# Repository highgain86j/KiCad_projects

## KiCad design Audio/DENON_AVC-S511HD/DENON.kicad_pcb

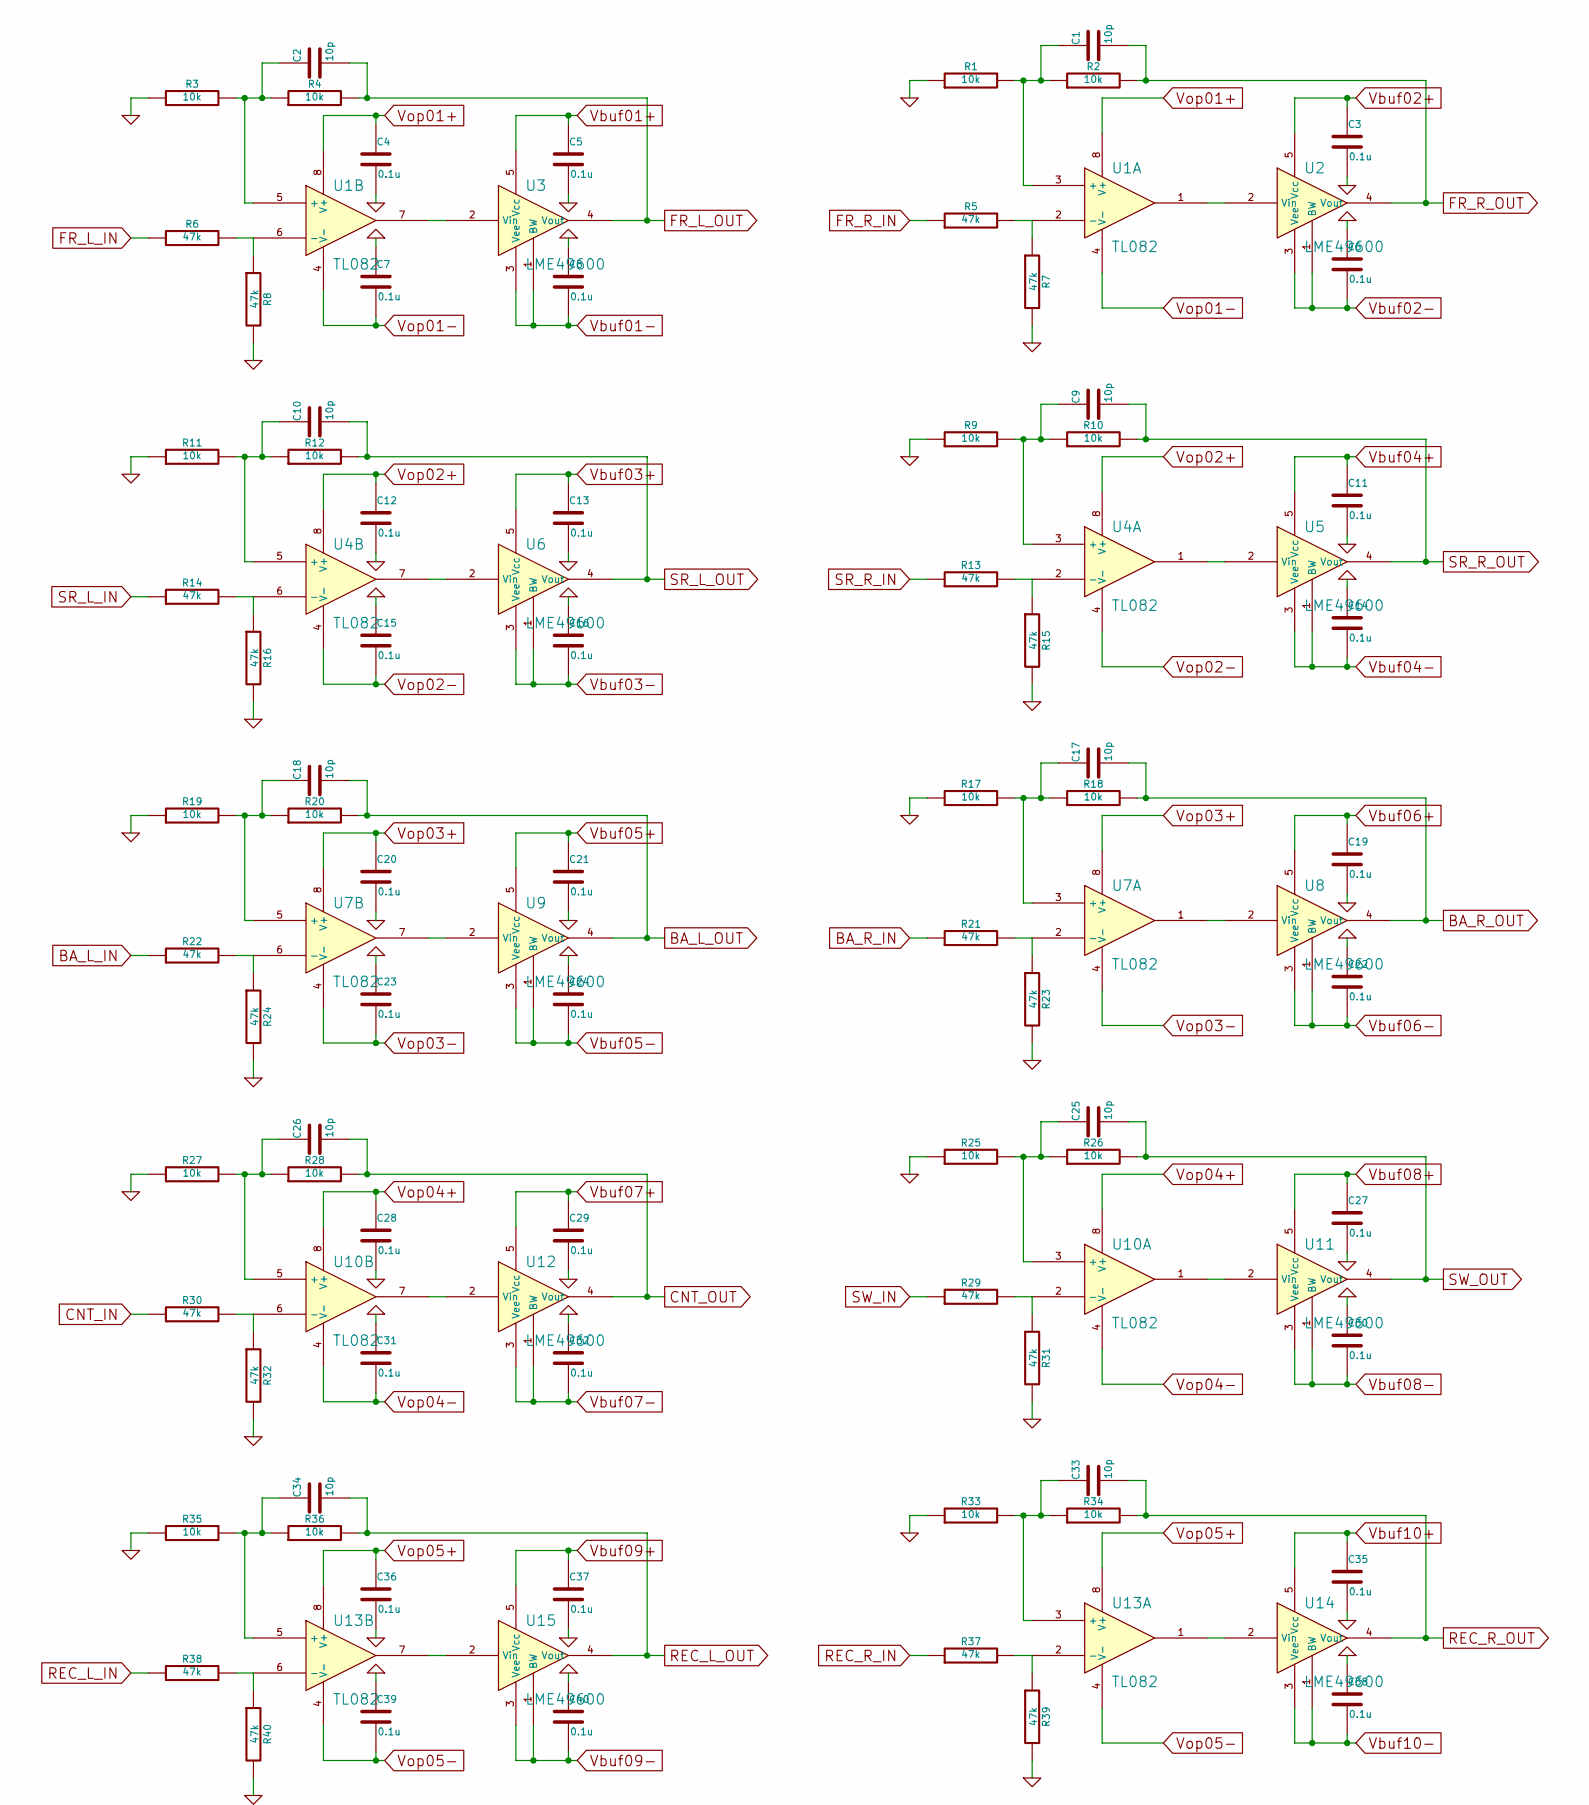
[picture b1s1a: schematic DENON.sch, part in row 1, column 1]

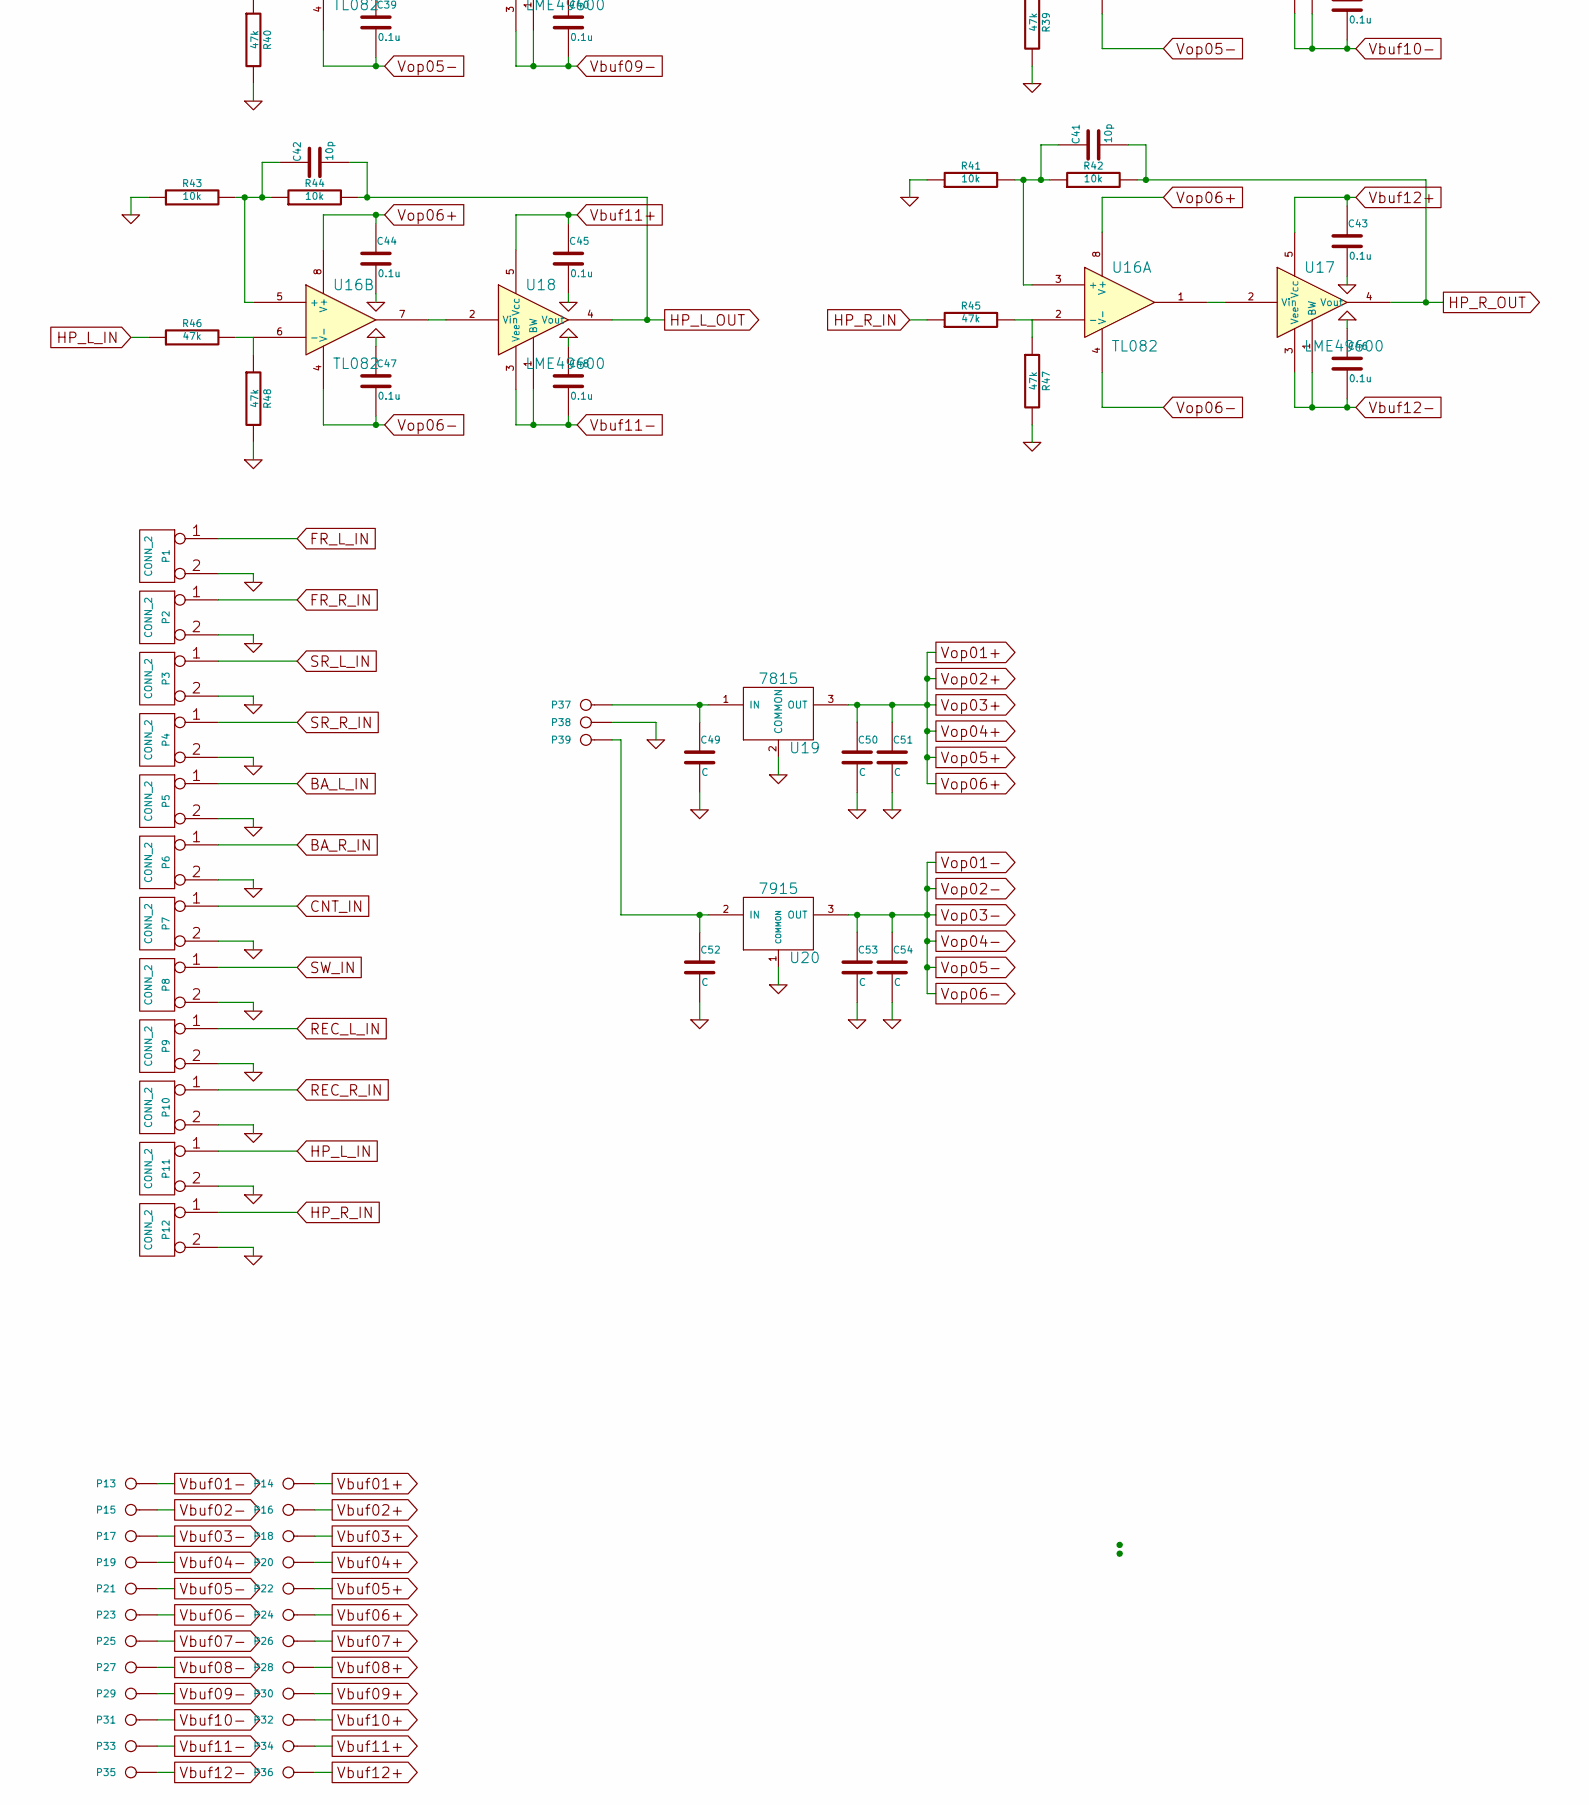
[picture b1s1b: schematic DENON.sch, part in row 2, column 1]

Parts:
C1, C2, C9, C10, C17, C18, C25, C26, C33, C34, C41, C42: 10p
C3, C4, C5, C6, C7, C8, C11, C12, C13, C14, C15, C16, C19, C20, C21, C22, C23, C24, C27, C28, C29, C30, C31, C32, C35, C36, C37, C38, C39, C40, C43, C44, C45, C46, C47, C48: 0.1u
C49, C50, C51, C52, C53, C54: C
P1, P2, P3, P4, P5, P6, P7, P8, P9, P10, P11, P12: CONN_2
P13, P14, P15, P16, P17, P18, P19, P20, P21, P22, P23, P24, P25, P26, P27, P28, P29, P30, P31, P32, P33, P34, P35, P36, P37, P38, P39: CONN_1
R1, R2, R3, R4, R9, R10, R11, R12, R17, R18, R19, R20, R25, R26, R27, R28, R33, R34, R35, R36, R41, R42, R43, R44: 10k
R5, R6, R7, R8, R13, R14, R15, R16, R21, R22, R23, R24, R29, R30, R31, R32, R37, R38, R39, R40, R45, R46, R47, R48: 47k
U1, U4, U7, U10, U13, U16: TL082
U2, U3, U5, U6, U8, U9, U11, U12, U14, U15, U17, U18: LME49600
U19: 7815
U20: 7915

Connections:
BA_L_IN: P5.1, R22.1
BA_L_OUT: C18.2, R20.2, U9.4 (Vout)
BA_R_IN: P6.1, R21.1
BA_R_OUT: C17.2, R18.2, U8.4 (Vout)
CNT_IN: P7.1, R30.1
CNT_OUT: C26.2, R28.2, U12.4 (Vout)
FR_L_IN: P1.1, R6.1
FR_L_OUT: C2.2, R4.2, U3.4 (Vout)
FR_R_IN: P2.1, R5.1
FR_R_OUT: C1.2, R2.2, U2.4 (Vout)
GND: C3.2, C4.2, C5.2, C6.1, C7.1, C8.1, C11.2, C12.2, C13.2, C14.1, C15.1, C16.1, C19.2, C20.2, C21.2, C22.1, C23.1, C24.1, C27.2, C28.2, C29.2, C30.1, C31.1, C32.1, C35.2, C36.2, C37.2, C38.1, C39.1, C40.1, C43.2, C44.2, C45.2, C46.1, C47.1, C48.1, C49.2, C50.2, C51.2, C52.2, C53.2, C54.2, P1.2 (PM), P2.2 (PM), P3.2 (PM), P4.2 (PM), P5.2 (PM), P6.2 (PM), P7.2 (PM), P8.2 (PM), P9.2 (PM), P10.2 (PM), P11.2 (PM), P12.2 (PM), P38.1, R1.1, R3.1, R7.2, R8.2, R9.1, R11.1, R15.2, R16.2, R17.1, R19.1, R23.2, R24.2, R25.1, R27.1, R31.2, R32.2, R33.1, R35.1, R39.2, R40.2, R41.1, R43.1, R47.2, R48.2, U19.2 (COMMON), U20.1 (COMMON)
HP_L_IN: P11.1, R46.1
HP_L_OUT: C42.2, R44.2, U18.4 (Vout)
HP_R_IN: P12.1, R45.1
HP_R_OUT: C41.2, R42.2, U17.4 (Vout)
unnamed: R30.2, R32.1, U10.6 (-)
unnamed: C26.1, R27.2, R28.1, U10.5 (+)
unnamed: U10.7, U12.2 (Vin)
unnamed: C17.1, R17.2, R18.1, U7.3 (+)
unnamed: U7.1, U8.2 (Vin)
unnamed: R21.2, R23.1, U7.2 (-)
unnamed: R38.2, R40.1, U13.6 (-)
unnamed: C34.1, R35.2, R36.1, U13.5 (+)
unnamed: U13.7, U15.2 (Vin)
unnamed: R29.2, R31.1, U10.2 (-)
unnamed: C25.1, R25.2, R26.1, U10.3 (+)
unnamed: U10.1, U11.2 (Vin)
unnamed: U4.7, U6.2 (Vin)
unnamed: R14.2, R16.1, U4.6 (-)
unnamed: C10.1, R11.2, R12.1, U4.5 (+)
unnamed: R5.2, R7.1, U1.2 (-)
unnamed: C1.1, R1.2, R2.1, U1.3 (+)
unnamed: U1.1, U2.2 (Vin)
unnamed: R22.2, R24.1, U7.6 (-)
unnamed: U7.7, U9.2 (Vin)
unnamed: C18.1, R19.2, R20.1, U7.5 (+)
unnamed: R13.2, R15.1, U4.2 (-)
unnamed: C9.1, R9.2, R10.1, U4.3 (+)
unnamed: U4.1, U5.2 (Vin)
unnamed: C49.1, P37.1, U19.1 (IN)
unnamed: C52.1, P39.1, U20.2 (IN)
unnamed: C33.1, R33.2, R34.1, U13.3 (+)
unnamed: U13.1, U14.2 (Vin)
unnamed: R37.2, R39.1, U13.2 (-)
unnamed: R45.2, R47.1, U16.2 (-)
unnamed: U16.1, U17.2 (Vin)
unnamed: R46.2, R48.1, U16.6 (-)
unnamed: U16.7, U18.2 (Vin)
unnamed: C42.1, R43.2, R44.1, U16.5 (+)
unnamed: U1.7, U3.2 (Vin)
unnamed: R6.2, R8.1, U1.6 (-)
unnamed: C2.1, R3.2, R4.1, U1.5 (+)
unnamed: C41.1, R41.2, R42.1, U16.3 (+)
REC_L_IN: P9.1, R38.1
REC_L_OUT: C34.2, R36.2, U15.4 (Vout)
REC_R_IN: P10.1, R37.1
REC_R_OUT: C33.2, R34.2, U14.4 (Vout)
SR_L_IN: P3.1, R14.1
SR_L_OUT: C10.2, R12.2, U6.4 (Vout)
SR_R_IN: P4.1, R13.1
SR_R_OUT: C9.2, R10.2, U5.4 (Vout)
SW_IN: P8.1, R29.1
SW_OUT: C25.2, R26.2, U11.4 (Vout)
Vbuf01+: C5.1, P14.1, U3.5 (Vcc)
Vbuf01-: C8.2, P13.1, U3.1 (BW), U3.3 (Vee)
Vbuf02+: C3.1, P16.1, U2.5 (Vcc)
Vbuf02-: C6.2, P15.1, U2.1 (BW), U2.3 (Vee)
Vbuf03+: C13.1, P18.1, U6.5 (Vcc)
Vbuf03-: C16.2, P17.1, U6.1 (BW), U6.3 (Vee)
Vbuf04+: C11.1, P20.1, U5.5 (Vcc)
Vbuf04-: C14.2, P19.1, U5.1 (BW), U5.3 (Vee)
Vbuf05+: C21.1, P22.1, U9.5 (Vcc)
Vbuf05-: C24.2, P21.1, U9.1 (BW), U9.3 (Vee)
Vbuf06+: C19.1, P24.1, U8.5 (Vcc)
Vbuf06-: C22.2, P23.1, U8.1 (BW), U8.3 (Vee)
Vbuf07+: C29.1, P26.1, U12.5 (Vcc)
Vbuf07-: C32.2, P25.1, U12.1 (BW), U12.3 (Vee)
Vbuf08+: C27.1, P28.1, U11.5 (Vcc)
Vbuf08-: C30.2, P27.1, U11.1 (BW), U11.3 (Vee)
Vbuf09+: C37.1, P30.1, U15.5 (Vcc)
Vbuf09-: C40.2, P29.1, U15.1 (BW), U15.3 (Vee)
Vbuf10+: C35.1, P32.1, U14.5 (Vcc)
Vbuf10-: C38.2, P31.1, U14.1 (BW), U14.3 (Vee)
Vbuf11+: C45.1, P34.1, U18.5 (Vcc)
Vbuf11-: C48.2, P33.1, U18.1 (BW), U18.3 (Vee)
Vbuf12+: C43.1, P36.1, U17.5 (Vcc)
Vbuf12-: C46.2, P35.1, U17.1 (BW), U17.3 (Vee)
Vop01+: C4.1, C12.1, C20.1, C28.1, C36.1, C44.1, C50.1, C51.1, U1.8 (V+), U4.8 (V+), U7.8 (V+), U10.8 (V+), U13.8 (V+), U16.8 (V+), U19.3 (OUT)
Vop01-: C7.2, C15.2, C23.2, C31.2, C39.2, C47.2, C53.1, C54.1, U1.4 (V-), U4.4 (V-), U7.4 (V-), U10.4 (V-), U13.4 (V-), U16.4 (V-), U20.3 (OUT)

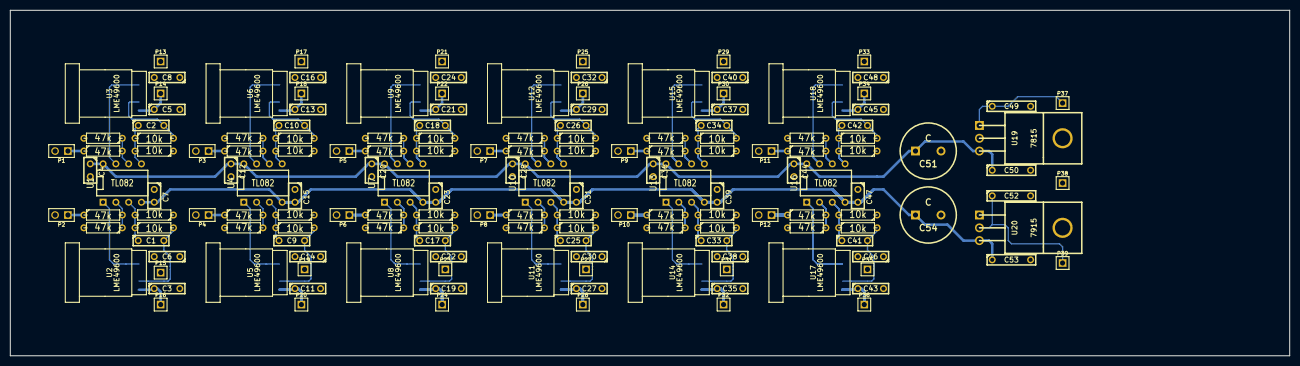
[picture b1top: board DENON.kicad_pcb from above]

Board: 2 copper layers, 254.0 x 68.6 mm, 161 parts (0 on the bottom side), 89 nets.

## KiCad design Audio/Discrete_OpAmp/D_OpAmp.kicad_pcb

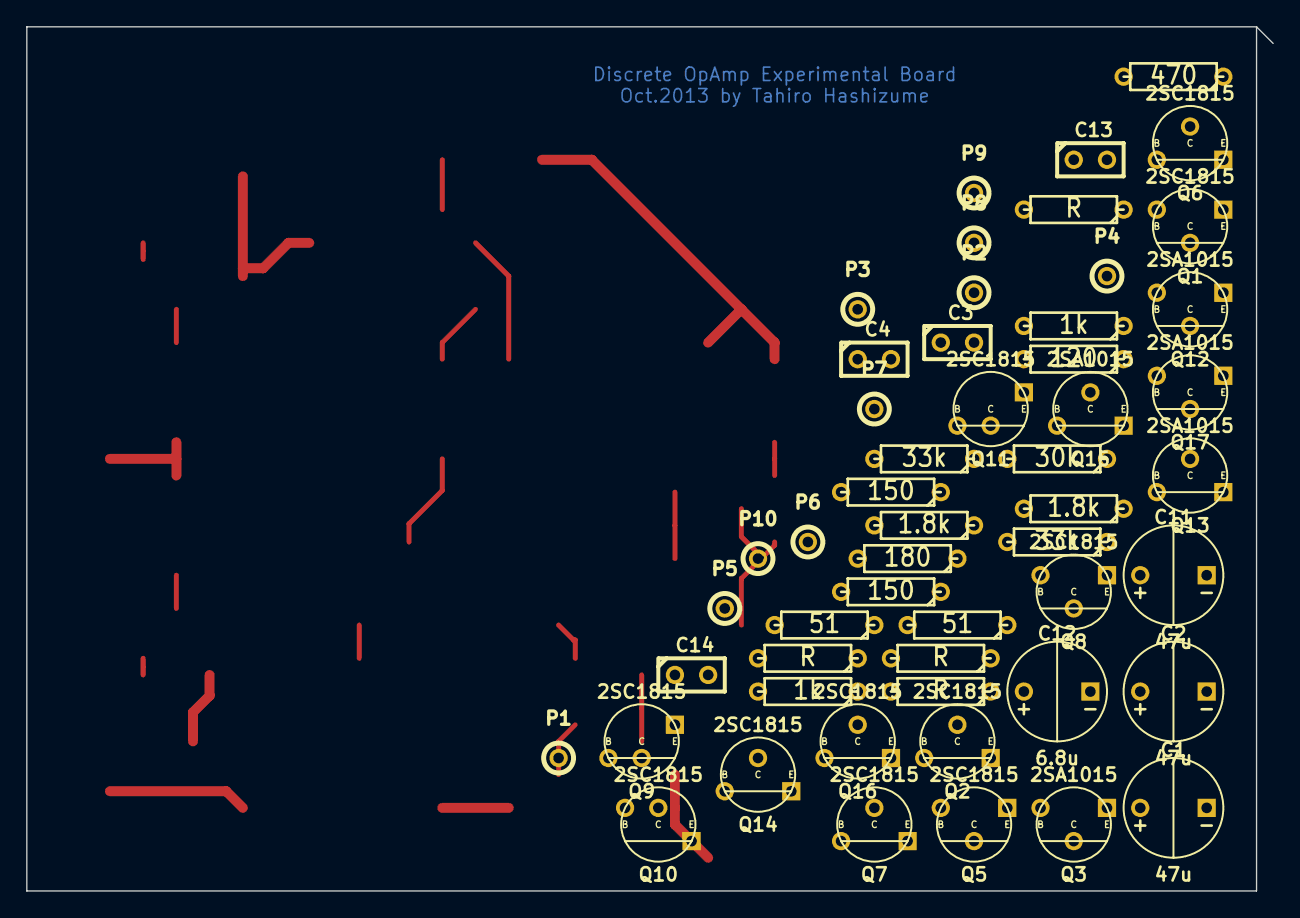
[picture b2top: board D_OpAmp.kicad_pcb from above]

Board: 2 copper layers, 95.2 x 66.0 mm, 52 parts (0 on the bottom side), 32 nets.

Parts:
C1, C2, C11: 47u; CE2-S
C3, C4: 0.1u; C1
C12: 6.8u; CE2-S
C13: 47p; C1
C14: 150p; C1
P1, P2, P3, P4, P5, P6, P7, P8, P9, P10: CONN_1; 1pin_small
Q1, Q5, Q8: 2SC1815; TO92-ECB3
Q2, Q6, Q7, Q14, Q16: 2SC1815; TO92-ECB2
Q3, Q12, Q17: 2SA1015; TO92-ECB3
Q9, Q11: 2SC1815; TO92-ECB5
Q10: 2SC1815; TO92-ECB6
Q13, Q15: 2SA1015; TO92-ECB2
R1, R2, R3, R4: R; R3
R7, R11: 33k; R3
R8, R10: 1.8k; R3
R9: 470; R3
R12, R15: 1k; R3
R13, R16: 51; R3
R14: 180; R3
R17: 30k; R3
R18, R20: 150; R3
R19: 120; R3

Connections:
GND: C1.2, C2.1, C3.2, C4.2, C12.2, P2.1, P8.1, P9.1, R7.2
unnamed: C12.1, R10.2
unnamed: C13.2, R9.2
unnamed: Q16.1, R20.1
unnamed: Q14.1, R18.1
unnamed: Q1.3, R1.1, R2.1
unnamed: Q1.1, Q3.3, Q16.2, R2.2
unnamed: C14.2, Q1.2, Q2.3, Q15.2, R1.2
unnamed: C11.2, R8.2
unnamed: C14.1, Q7.2, Q17.3, R15.2
unnamed: Q12.1, Q17.1, R19.2
unnamed: Q15.1, Q17.2
unnamed: Q12.2, Q13.1
unnamed: Q6.3, Q8.2, R17.1
unnamed: Q6.2, R13.2, R16.2
unnamed: Q5.1, R13.1
unnamed: Q7.1, R16.1
unnamed: Q5.2, Q12.3, R12.2
unnamed: Q6.1, Q8.3, R14.1
unnamed: Q11.1, R17.2
unnamed: Q13.2, Q14.2, Q14.3, Q16.3
unnamed: Q9.1, Q10.2, Q10.3
unnamed: Q10.1, Q11.2, Q11.3, Q13.3, Q15.3
NEG: Q5.3, R9.1, R10.1, R11.1
NFB: P7.1, R11.2
OUT: P10.1, R3.1, R4.1
OUT_BH: P5.1, Q2.1, R3.2
OUT_BL: P6.1, Q3.1, R4.2
POS: C13.1, Q7.3, R7.1, R8.1
SIG: C11.1, P4.1
V+: C1.1, C3.1, P1.1, Q2.2, Q9.2, Q9.3, R12.1, R15.1, R19.1
V-: C2.2, C4.1, P3.1, Q3.2, Q8.1, R14.2, R18.2, R20.2

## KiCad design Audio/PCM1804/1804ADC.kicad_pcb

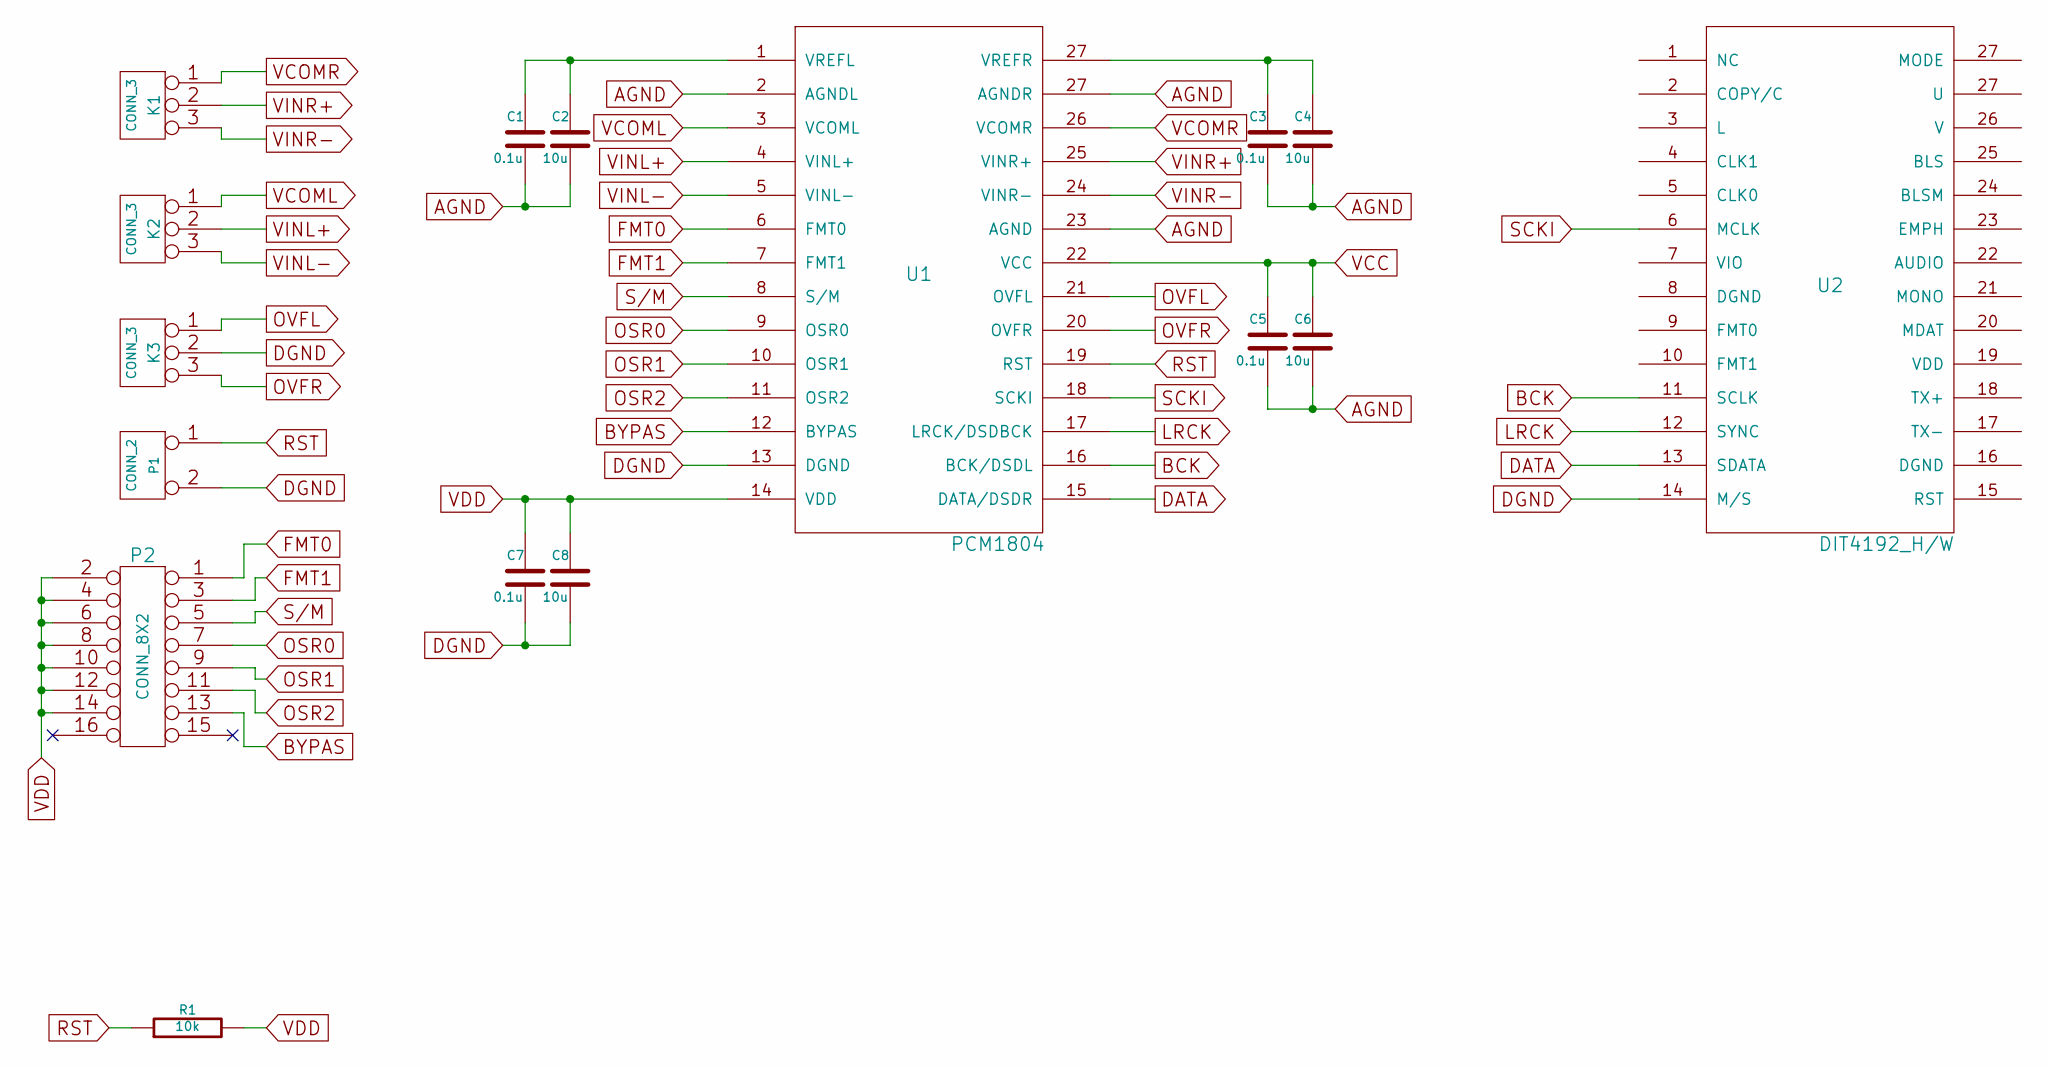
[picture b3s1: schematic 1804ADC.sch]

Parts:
C1, C3, C5, C7: 0.1u
C2, C4, C6, C8: 10u
K1, K2, K3: CONN_3
P1: CONN_2
P2: CONN_8X2
R1: 10k
U1: PCM1804
U2: DIT4192_H/W

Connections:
BCK: U1.16 (BCK/DSDL), U2.11 (SCLK)
BYPAS: P2.13, U1.12 (BYPAS)
DATA: U1.15 (DATA/DSDR), U2.13 (SDATA)
DGND: C7.2, C8.2, K3.2 (PM), P1.2 (PM), U1.13 (DGND), U2.14 (M/S)
FMT0: P2.1, U1.6 (FMT0)
FMT1: P2.3, U1.7 (FMT1)
LRCK: U1.17 (LRCK/DSDBCK), U2.12 (SYNC)
unnamed: C1.1, C2.1, U1.1 (VREFL)
OSR0: P2.7, U1.9 (OSR0)
OSR1: P2.9, U1.10 (OSR1)
OSR2: P2.11, U1.11 (OSR2)
OVFL: K3.1, U1.21 (OVFL)
OVFR: K3.3, U1.20 (OVFR)
RST: P1.1, R1.1, U1.19 (RST)
S/M: P2.5, U1.8 (S/M)
SCKI: U1.18 (SCKI), U2.6 (MCLK)
VCC: C5.1, C6.1, U1.22 (VCC)
VCOML: K2.1, U1.3 (VCOML)
VCOMR: K1.1, U1.26 (VCOMR)
VDD: C7.1, C8.1, P2.2, P2.4, P2.6, P2.8, P2.10, P2.12, P2.14, R1.2, U1.14 (VDD)
VINL+: K2.2 (PM), U1.4 (VINL+)
VINL-: K2.3, U1.5 (VINL-)
VINR+: K1.2 (PM), U1.25 (VINR+)
VINR-: K1.3, U1.24 (VINR-)

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
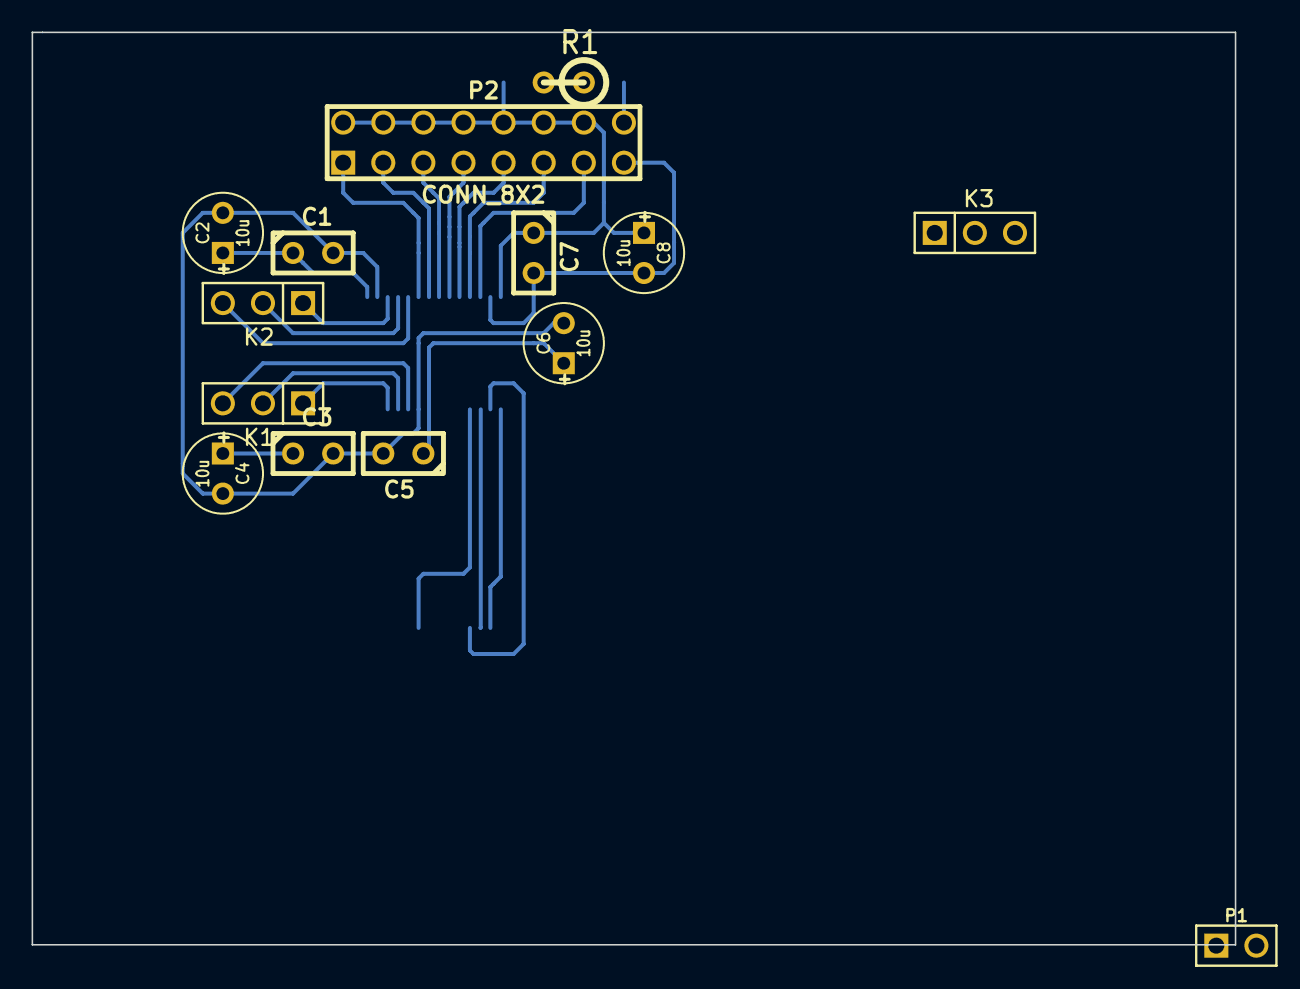
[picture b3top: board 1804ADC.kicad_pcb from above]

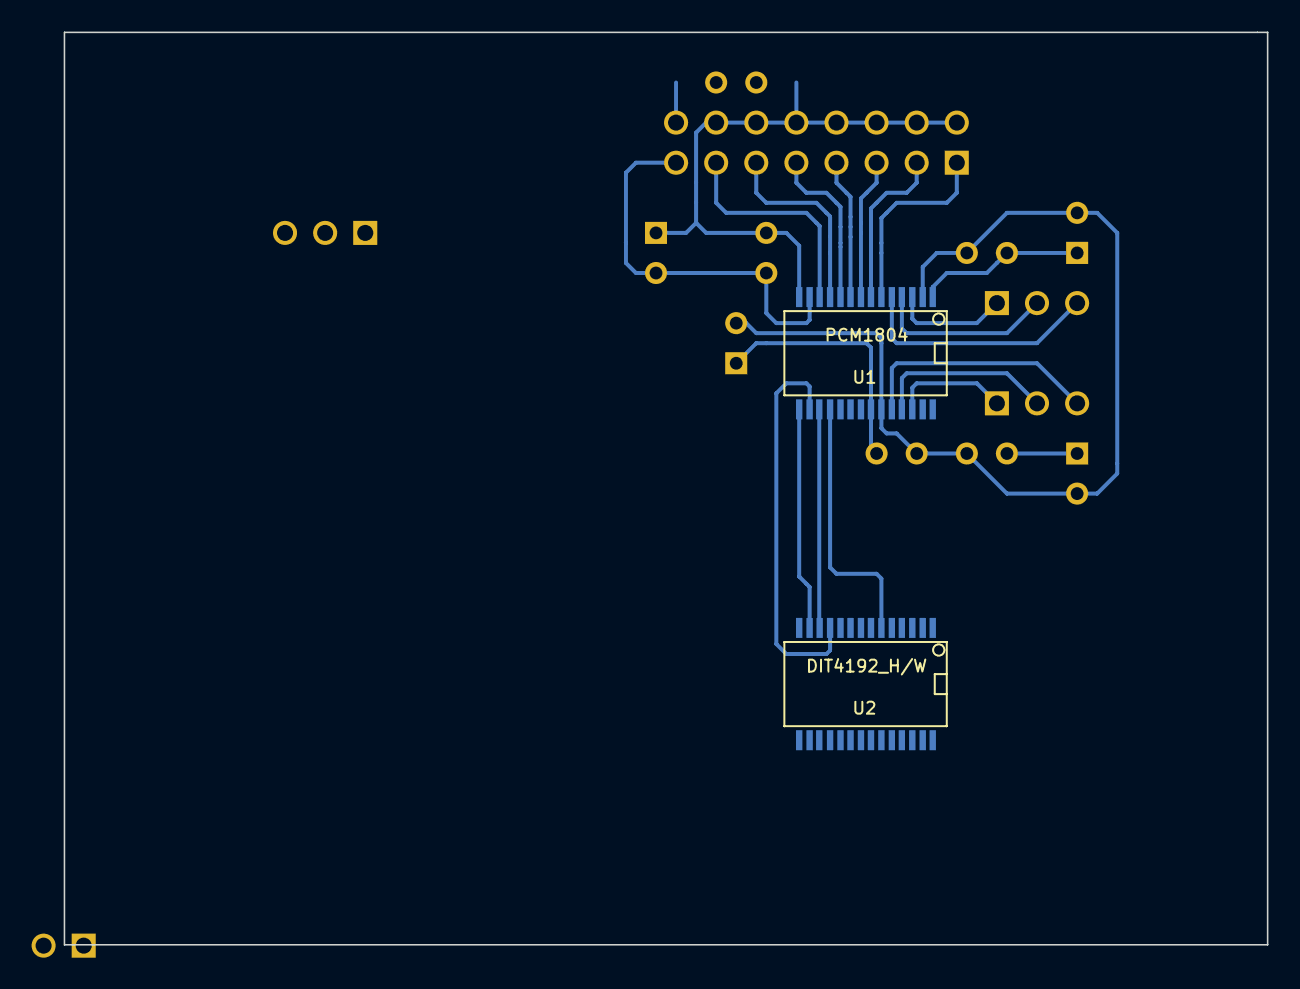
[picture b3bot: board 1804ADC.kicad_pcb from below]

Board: 2 copper layers, 76.2 x 57.8 mm, 16 parts (2 on the bottom side), 26 nets.
